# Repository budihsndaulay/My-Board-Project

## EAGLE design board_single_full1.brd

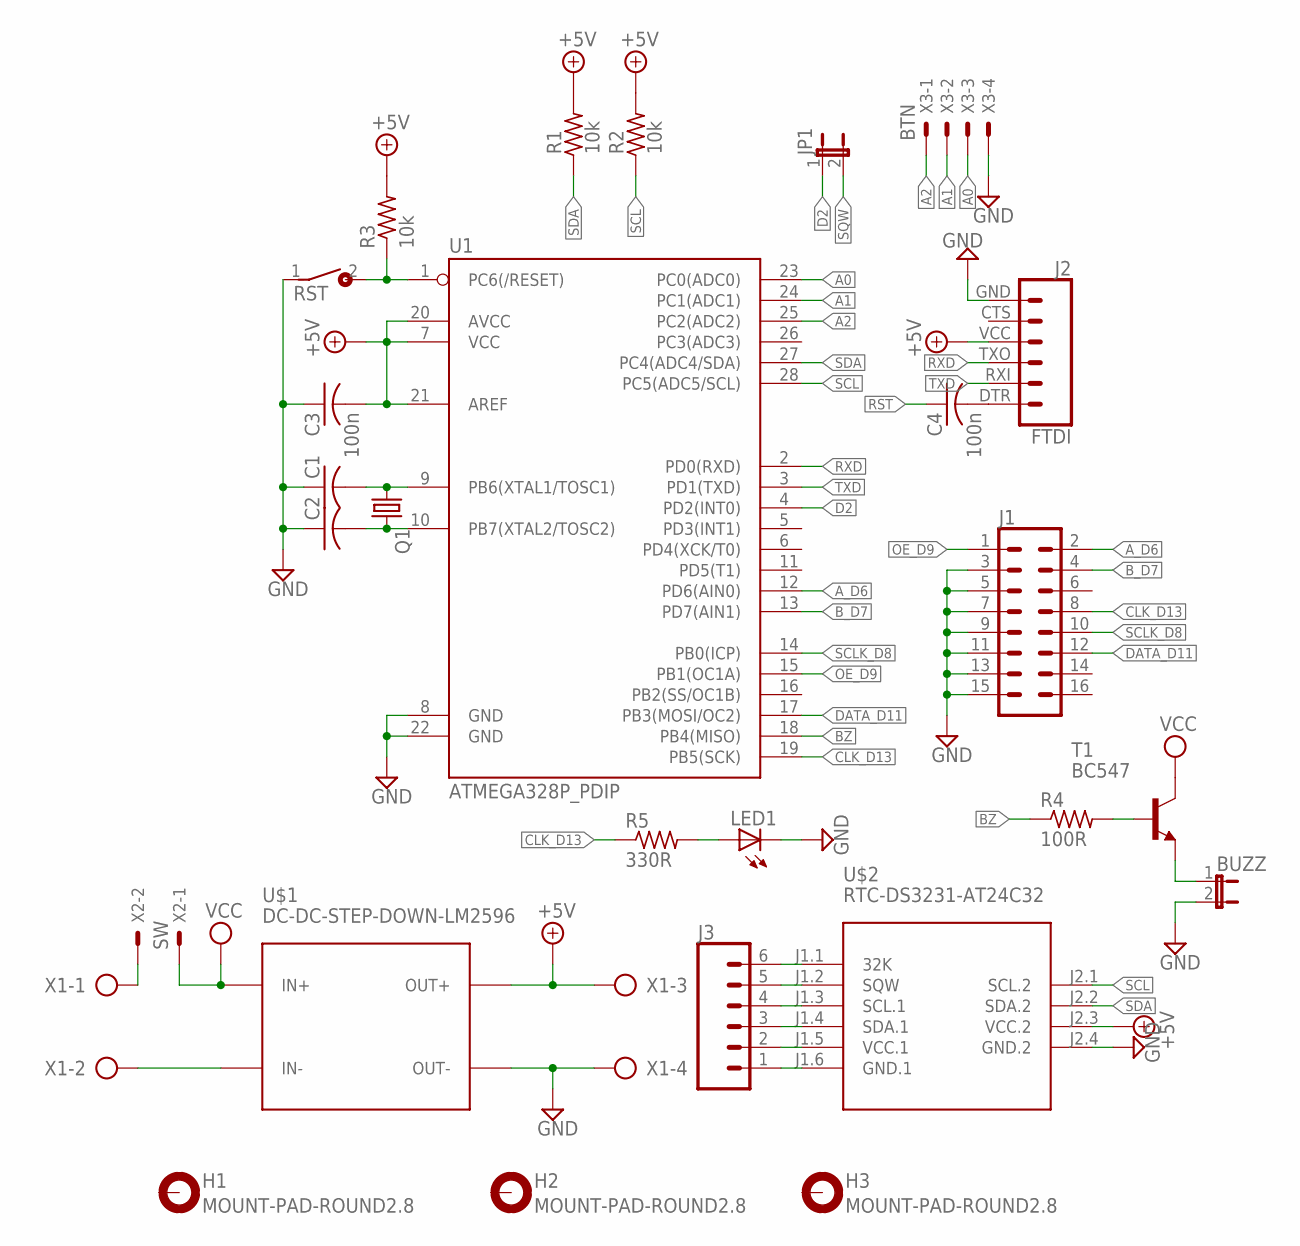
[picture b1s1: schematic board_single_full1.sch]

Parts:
BUZZ: JP1E; JP1
C1, C2: C-USC0603K; C0603K
C3, C4: 100n; C0603K
H1, H2, H3: MOUNT-PAD-ROUND2.8; 2,8-PAD
J1: CONN_08X2_SHROUD; 2X8-SHROUDED_LOCK
J2: FTDI; FTDI_BASIC
J3: CONN_06NO_SILK_FEMALE_PTH; 1X06_NO_SILK
JP1: JP1E; JP1
LED1: LED3MM
Q1: CRYSTALHC49U-V; HC49U-V
R1, R2: 10k; 0207/7
R3: 10k; R0603
R4: 100R; R0603
R5: 330R; R0603
RST: DS01E; DS-01
T1: BC547; TO92
U1: ATMEGA328P_PDIP; DIL28-3
U$1: DC-DC-STEP-DOWN-LM2596
U$2: RTC-DS3231-AT24C32
X1: AK500/4
X2: SW; JST-XH-02-PACKAGE-LONG-PAD
X3: BTN; JST-XH-04-PACKAGE-LONG-PAD

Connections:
+5V: C3.2, J2.VCC (4), R1.2, R2.2, R3.2, U1.7 (VCC), U1.20 (AVCC), U1.21 (AREF), U$1.OUT+, U$2.J2.3 (VCC.2), X1.3
A0: U1.23 (PC0(ADC0)), X3.3
A1: U1.24 (PC1(ADC1)), X3.2
A2: U1.25 (PC2(ADC2)), X3.1
A_D6: J1.2, U1.12 (PD6(AIN0))
BZ: R4.1, U1.18 (PB4(MISO))
B_D7: J1.4, U1.13 (PD7(AIN1))
CLK_D13: J1.8, R5.1, U1.19 (PB5(SCK))
D2: JP1.1, U1.4 (PD2(INT0))
DATA_D11: J1.12, U1.17 (PB3(MOSI/OC2))
GND: BUZZ.2, C1.1, C2.1, C3.1, J1.3, J1.5, J1.7, J1.9, J1.11, J1.13, J1.15, J2.GND (6), LED1.K (C), RST.1, U1.8 (GND), U1.22 (GND), U$1.OUT-, U$2.J2.4 (GND.2), X1.4, X3.4
unnamed: X1.1, X2.2
unnamed: U$1.IN-, X1.2
unnamed: BUZZ.1, T1.1 (E)
unnamed: C1.2, Q1.1, U1.9 (PB6(XTAL1/TOSC1))
unnamed: C2.2, Q1.2, U1.10 (PB7(XTAL2/TOSC2))
unnamed: C4.2, J2.DTR (1)
unnamed: J3.1, U$2.J1.6 (GND.1)
unnamed: J3.2, U$2.J1.5 (VCC.1)
unnamed: J3.3, U$2.J1.4 (SDA.1)
unnamed: J3.4, U$2.J1.3 (SCL.1)
unnamed: R4.2, T1.2 (B)
unnamed: J3.6, U$2.J1.1 (32K)
unnamed: LED1.A, R5.2
OE_D9: J1.1, U1.15 (PB1(OC1A))
RST: C4.1, R3.1, RST.2, U1.1 (PC6(/RESET))
RXD: J2.TXO (3), U1.2 (PD0(RXD))
SCL: R2.1, U1.28 (PC5(ADC5/SCL)), U$2.J2.1 (SCL.2)
SCLK_D8: J1.10, U1.14 (PB0(ICP))
SDA: R1.1, U1.27 (PC4(ADC4/SDA)), U$2.J2.2 (SDA.2)
SQW: J3.5, JP1.2, U$2.J1.2 (SQW)
TXD: J2.RXI (2), U1.3 (PD1(TXD))
VCC: T1.3 (C), U$1.IN+, X2.1

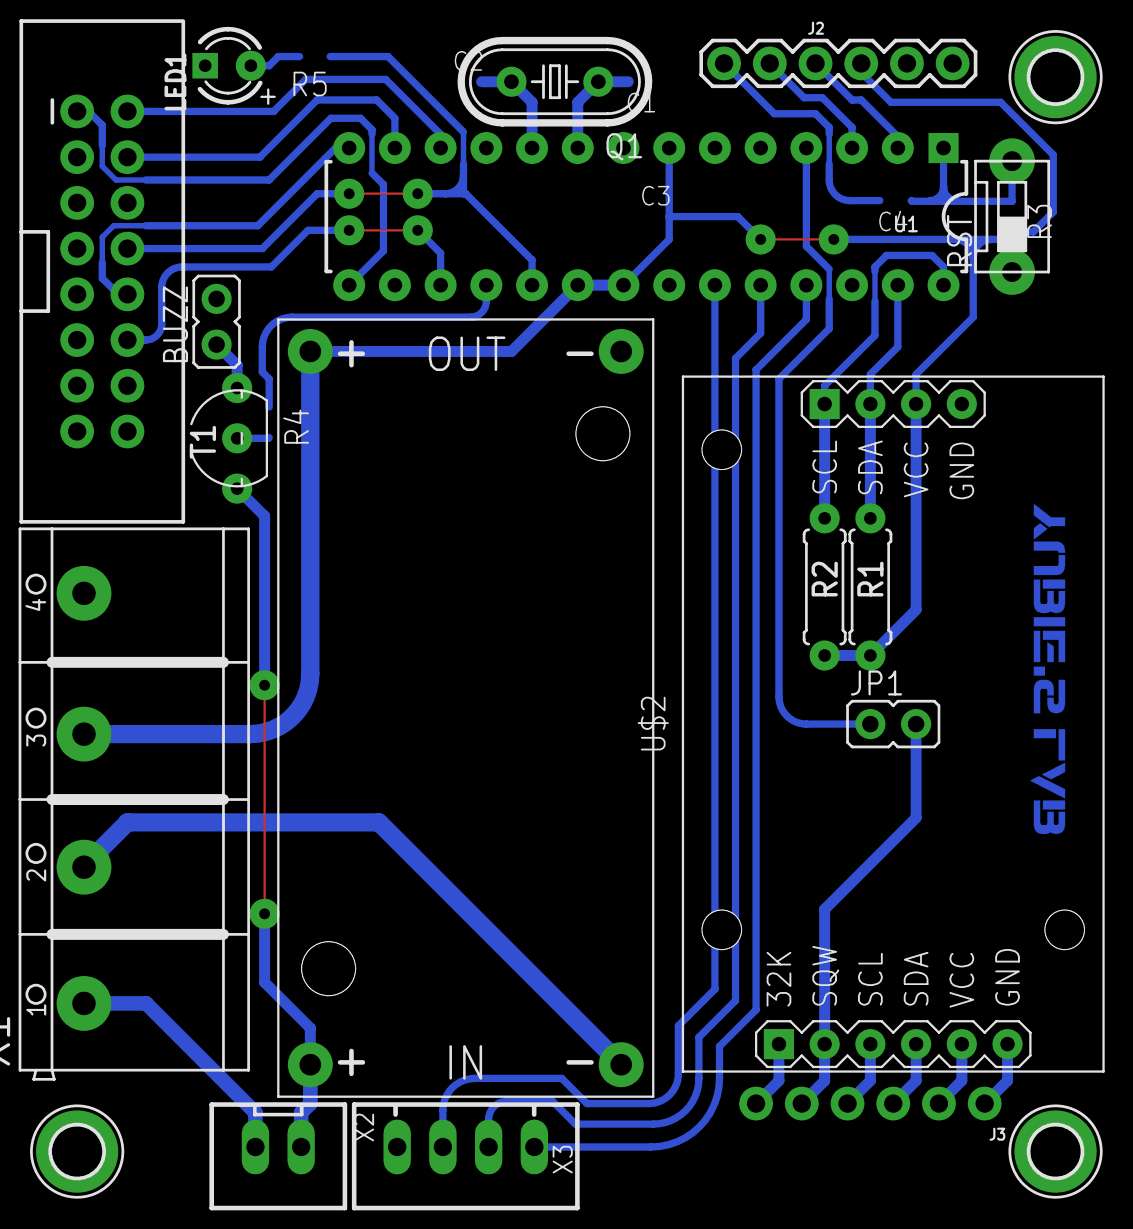
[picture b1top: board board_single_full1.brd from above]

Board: 2 copper layers, 27 parts (0 on the bottom side), 33 nets.

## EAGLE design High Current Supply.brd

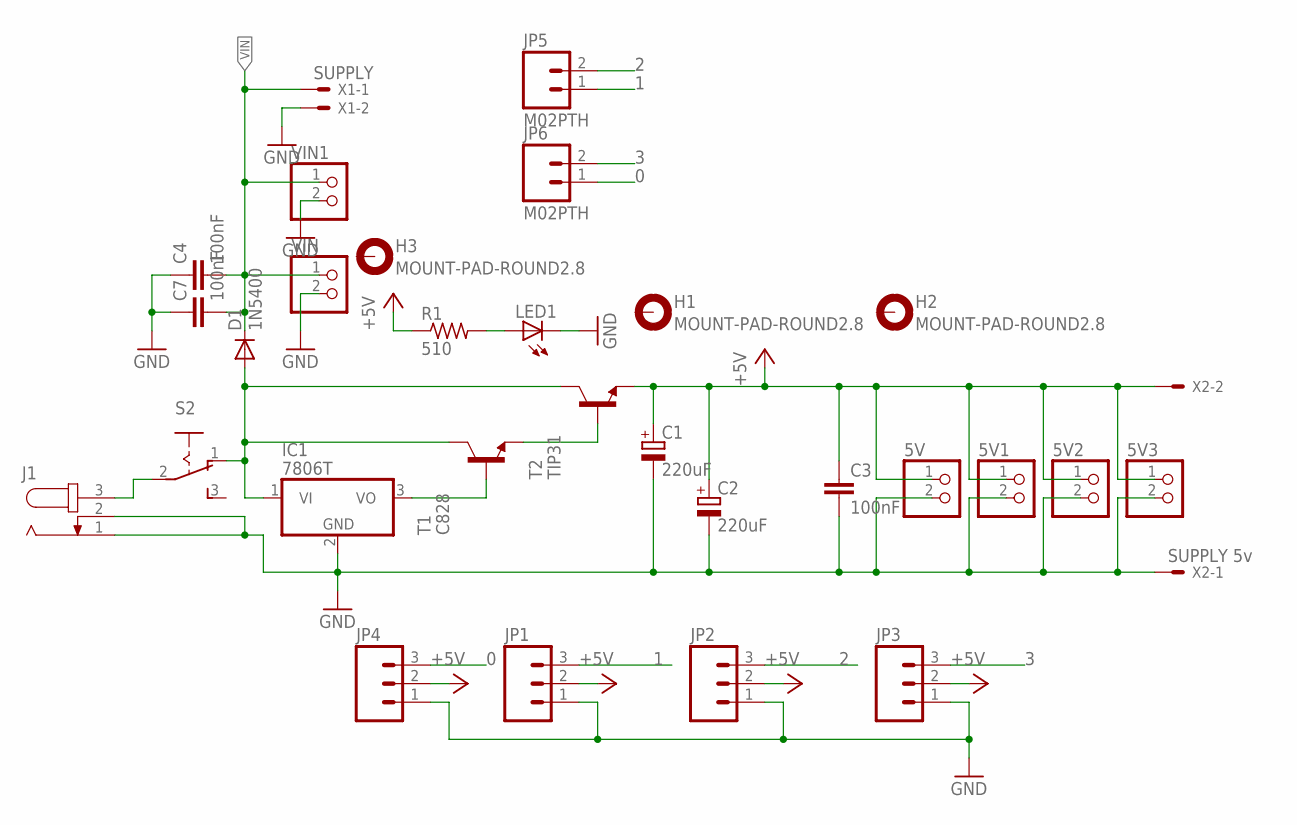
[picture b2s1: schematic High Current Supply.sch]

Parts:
5V, 5V1, 5V2, 5V3: PINHD-1X2; 1X02
C1, C2: 220uF; E2,5-7
C3, C4, C7: 100nF; C5B3
D1: 1N5400; DO201-15
H1, H2, H3: MOUNT-PAD-ROUND2.8; 2,8-PAD
IC1: 7806T; TO220H
J1: JACK-PLUG1; SPC4078
JP1, JP2, JP3, JP4: M03PTH; 1X03
JP5, JP6: M02PTH; 1X02
LED1: LED3MM
R1: 510; R0603
S2: 255SB
T1: C828; TO92-ECB
T2: TIP31; TO220
VIN, VIN1: PINHD-1X2; 1X02
X1: SUPPLY; JST-XH-02-PACKAGE-LONG-PAD
X2: SUPPLY 5v; JST-XH-02-PACKAGE-LONG-PAD

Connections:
0: JP4.3, JP6.1
1: JP1.3, JP5.1
2: JP2.3, JP5.2
3: JP3.3, JP6.2
+5V: 5V.1, 5V1.1, 5V2.1, 5V3.1, C1.+, C2.+, C3.1, JP1.2, JP2.2, JP3.2, JP4.2, R1.1, T2.3 (E), X2.2
GND: 5V.2, 5V1.2, 5V2.2, 5V3.2, C1.-, C2.-, C3.2, C4.1, C7.1, IC1.2 (GND), J1.1, J1.2, JP1.1, JP2.1, JP3.1, JP4.1, LED1.K (C), VIN.2, VIN1.2, X1.2, X2.1
unnamed: T1.E, T2.1 (B)
unnamed: J1.3, S2.2
unnamed: IC1.3 (VO), T1.B
unnamed: D1.A, IC1.1 (VI), S2.1 (O), T1.C, T2.2 (C)
unnamed: LED1.A, R1.2
VIN: C4.2, C7.2, D1.C, VIN.1, VIN1.1, X1.1

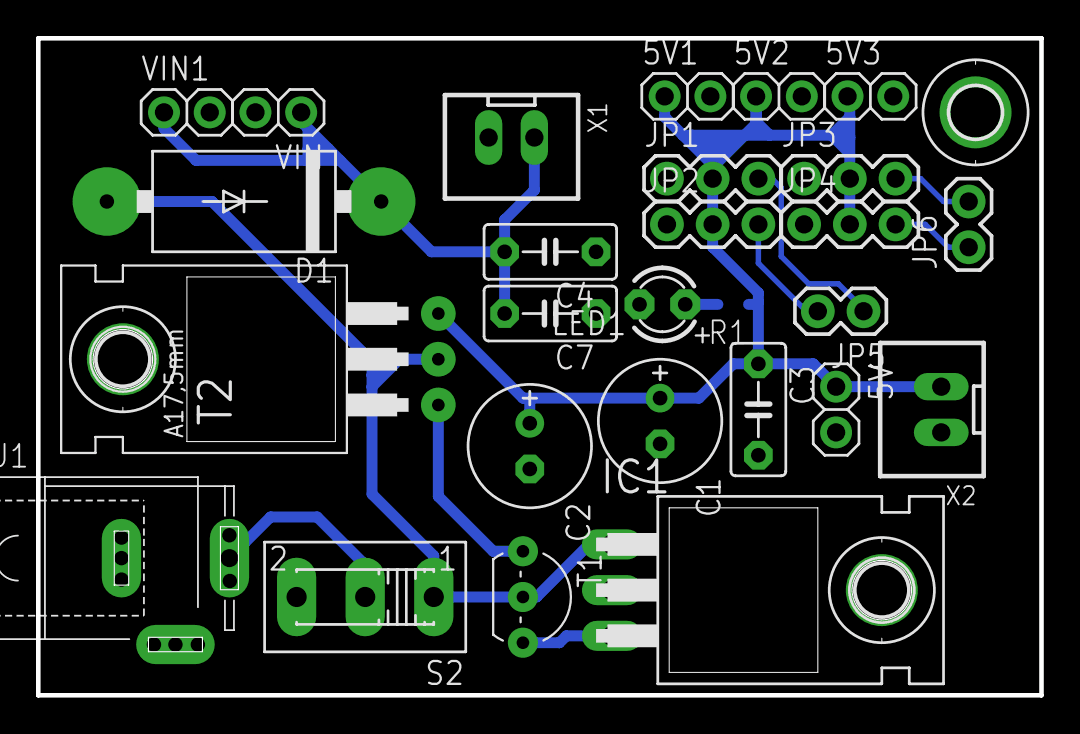
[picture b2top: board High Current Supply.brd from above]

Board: 2 copper layers, 55.7 x 36.5 mm, 30 parts (0 on the bottom side), 12 nets.

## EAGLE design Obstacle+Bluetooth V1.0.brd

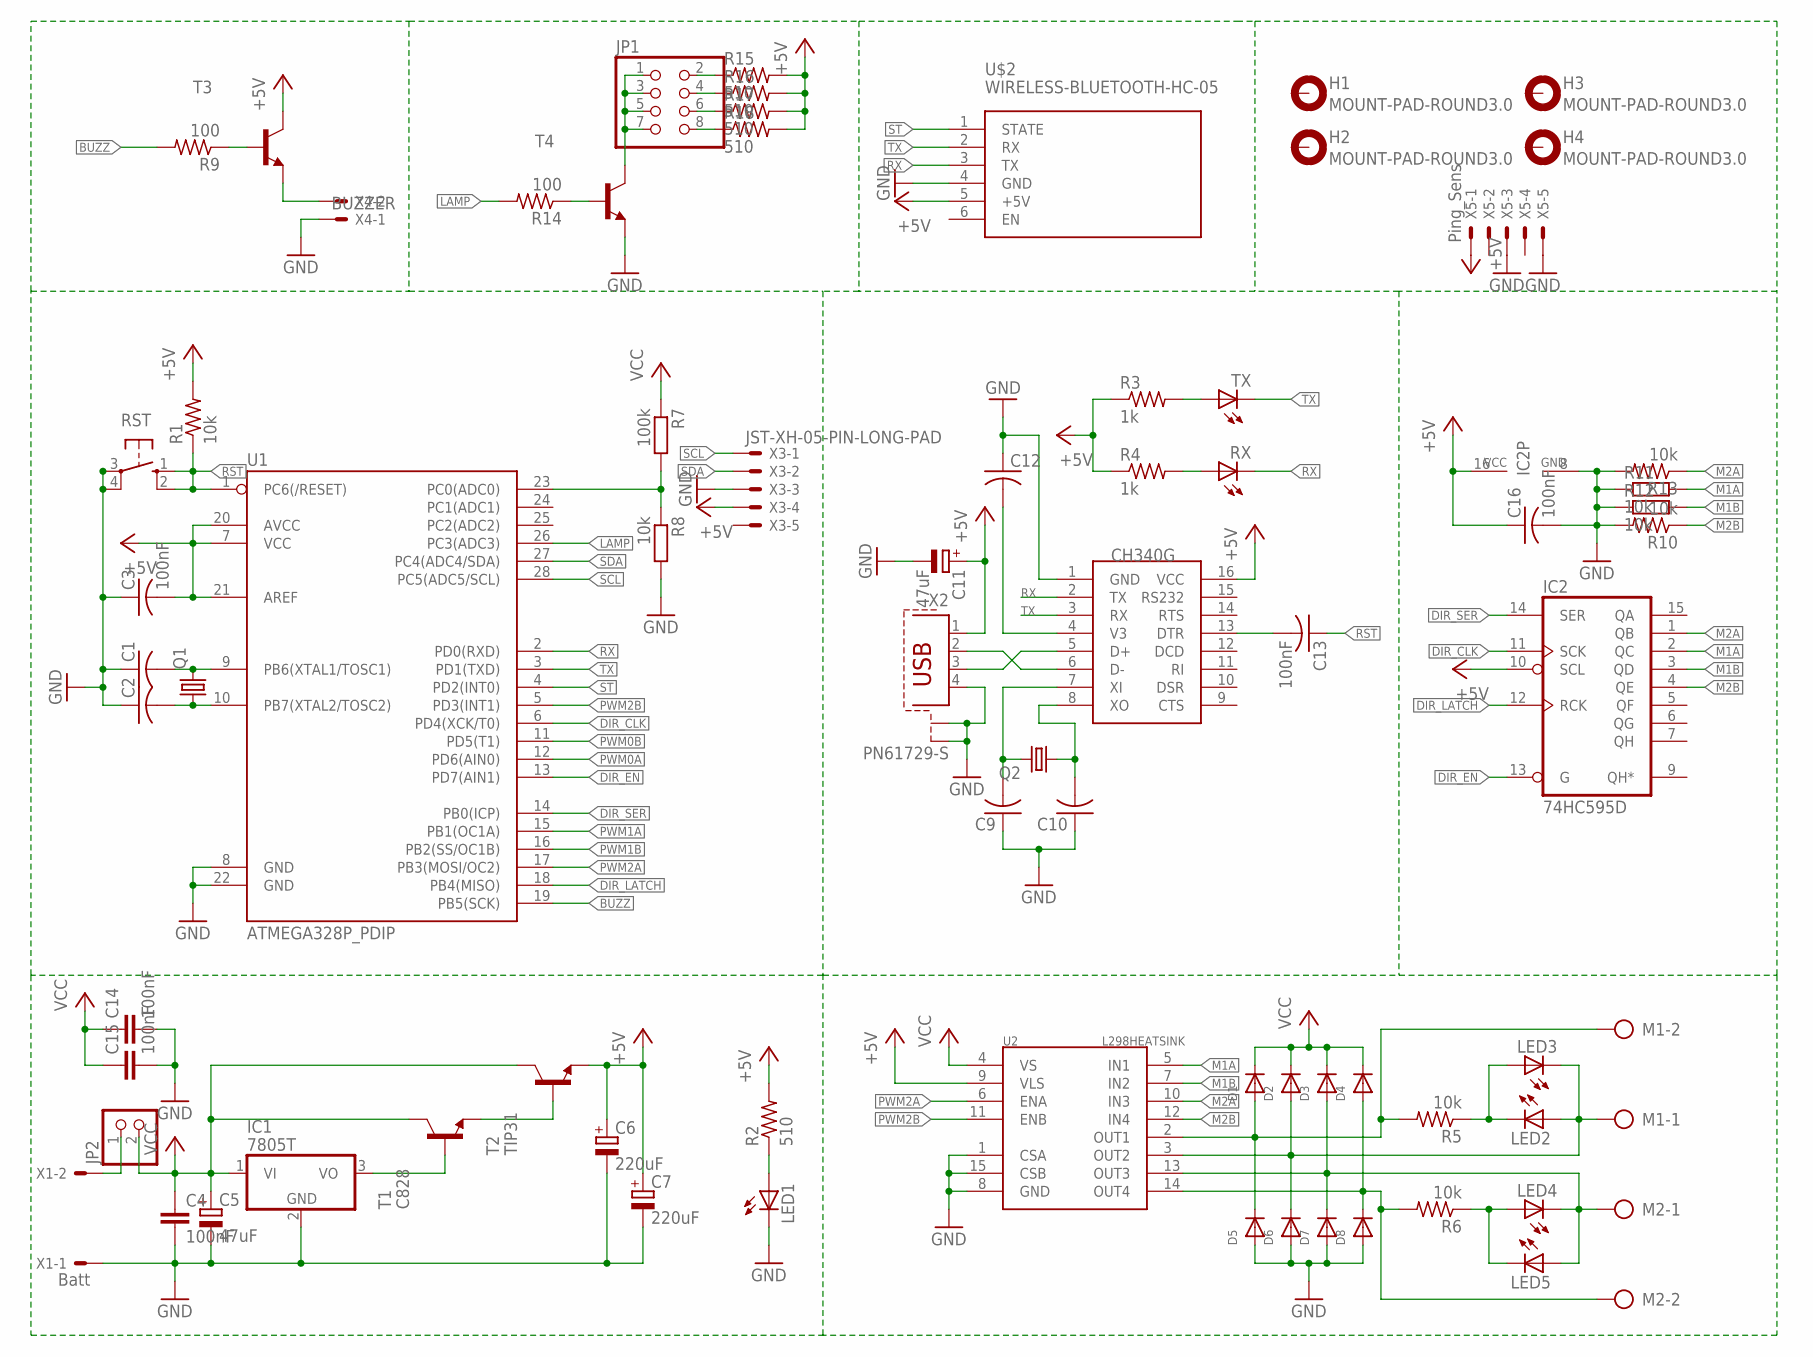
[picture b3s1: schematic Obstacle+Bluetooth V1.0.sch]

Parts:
C1, C2, C9, C10, C12: C-USC0603K; C0603K
C3, C13, C16: 100nF; C0603K
C4, C14, C15: 100nF; C5B2.5
C5, C11: 47uF; E2,5-7
C6, C7: 220uF; E2,5-5
D1, D2, D3, D4, D5, D6, D7, D8: DIODESMA; SMADIODE
H1, H2, H3, H4: MOUNT-PAD-ROUND3.0; 3,0-PAD
IC1: 7805T; TO220H
IC2: 74HC595D; SO16
JP1: PINHD-2X4; 2X04
JP2: PINHD-1X2; 1X02
LED1, LED2, LED3, LED4, LED5: LED3MM
M1, M2: AK500/2
Q1, Q2: CRYSTALHC49U-V; HC49U-V
R1, R5, R6, R10, R13: 10k; R0603
R2, R15, R16, R17, R18: 510; R0603
R3, R4: 1k; R0603
R7: 100k; 0207/7
R8, R11, R12: 10k; 0207/7
R9, R14: 100; R0603
RST: 10-XX; B3F-10XX
RX: LED3MM
T1: C828; TO92-ECB
T2: TIP31; TO220
T3, T4: -NPN-TO92L; TO92L
TX: LED3MM
U1: ATMEGA328P_PDIP; DIL28-3
U2: L298HEATSINK; MULTIWATT15_6400BGHEATSINK
U$1: CH340G; SOIC16
U$2: WIRELESS-BLUETOOTH-HC-05
X1: Batt; JST-XH-02-PACKAGE-LONG-PAD
X2: PN61729-S
X3: JST-XH-05-PIN-LONG-PAD; JST-XH-05-PACKAGE-LONG-PAD
X4: BUZZER; JST-XH-02-PACKAGE-LONG-PAD
X5: Ping_Sens; JST-XH-05-PACKAGE-LONG-PAD

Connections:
+5V: C3.2, C6.+, C7.+, C11.+, C16.1, IC2.10 (SCL), IC2.16 (VCC), R1.2, R2.2, R3.1, R4.1, R15.2, R16.2, R17.2, R18.2, T2.3 (E), T3.3 (C), U1.7 (VCC), U1.20 (AVCC), U1.21 (AREF), U2.9 (VLS), U$1.16 (VCC), U$2.5 (+5V), X2.1, X3.4, X5.1
BUZZ: R9.2, U1.19 (PB5(SCK))
DIR_CLK: IC2.11 (SCK), U1.6 (PD4(XCK/T0))
DIR_EN: IC2.13 (G), U1.13 (PD7(AIN1))
DIR_LATCH: IC2.12 (RCK), U1.18 (PB4(MISO))
DIR_SER: IC2.14 (SER), U1.14 (PB0(ICP))
GND: C1.1, C2.1, C3.1, C4.2, C5.-, C6.-, C7.-, C9.1, C10.1, C11.-, C12.1, C14.2, C15.2, C16.2, D5.A, D6.A, D7.A, D8.A, IC1.2 (GND), IC2.8 (GND), LED1.K (C), R8.2, R10.2, R11.1, R12.1, R13.2, RST.3, RST.4 (P1), T4.1 (E), U1.8 (GND), U1.22 (GND), U2.1 (CSA), U2.8 (GND), U2.15 (CSB), U$1.1 (GND), U$2.4 (GND), X1.1, X2.4, X2.S1, X2.S2, X3.3, X4.1, X5.3, X5.5
LAMP: R14.2, U1.26 (PC3(ADC3))
M1A: IC2.2 (QC), R11.2, U2.5 (IN1)
M1B: IC2.3 (QD), R12.2, U2.7 (IN2)
M2A: IC2.1 (QB), R13.1, U2.10 (IN3)
M2B: IC2.4 (QE), R10.1, U2.12 (IN4)
unnamed: C1.2, Q1.2, U1.9 (PB6(XTAL1/TOSC1))
unnamed: C2.2, Q1.1, U1.10 (PB7(XTAL2/TOSC2))
unnamed: C13.2, U$1.13 (DTR)
unnamed: R4.2, RX.A
unnamed: IC1.3 (VO), T1.B
unnamed: T1.E, T2.1 (B)
unnamed: R3.2, TX.A
unnamed: LED1.A, R2.1
unnamed: U$1.6 (D-), X2.2
unnamed: U$1.5 (D+), X2.3
unnamed: C9.2, Q2.2, U$1.7 (XI)
unnamed: C10.2, Q2.1, U$1.8 (XO)
unnamed: D2.A, D6.C, LED2.A, LED3.K (C), M1.1, U2.3 (OUT2)
unnamed: D3.A, D7.C, LED4.K (C), LED5.A, M2.1, U2.13 (OUT3)
unnamed: C12.2, U$1.4 (V3)
unnamed: D4.A, D8.C, M2.2, R6.2, U2.14 (OUT4)
unnamed: LED2.K (C), LED3.A, R5.1
unnamed: LED4.A, LED5.K (C), R6.1
unnamed: R7.2, R8.1, U1.23 (PC0(ADC0))
unnamed: T3.1 (E), X4.2
unnamed: R9.1, T3.2 (B)
unnamed: R14.1, T4.2 (B)
unnamed: JP2.1, X1.2
unnamed: JP1.1, JP1.3, JP1.5, JP1.7, T4.3 (C)
unnamed: JP1.2, R15.1
unnamed: JP1.4, R16.1
unnamed: JP1.6, R17.1
unnamed: JP1.8, R18.1
unnamed: D1.A, D5.C, M1.2, R5.2, U2.2 (OUT1)
PWM0A: U1.12 (PD6(AIN0))
PWM0B: U1.11 (PD5(T1))
PWM1A: U1.15 (PB1(OC1A))
PWM1B: U1.16 (PB2(SS/OC1B))
PWM2A: U1.17 (PB3(MOSI/OC2)), U2.6 (ENA)
PWM2B: U1.5 (PD3(INT1)), U2.11 (ENB)
RST: C13.1, R1.1, RST.1 (S), RST.2 (S1), U1.1 (PC6(/RESET))
RX: RX.K (C), U1.2 (PD0(RXD)), U$1.2 (TX), U$2.3 (TX)
SCL: U1.28 (PC5(ADC5/SCL)), X3.1
SDA: U1.27 (PC4(ADC4/SDA)), X3.2
ST: U1.4 (PD2(INT0)), U$2.1 (STATE)
TX: TX.K (C), U1.3 (PD1(TXD)), U$1.3 (RX), U$2.2 (RX)
VCC: C4.1, C5.+, C14.1, C15.1, D1.C, D2.C, D3.C, D4.C, IC1.1 (VI), JP2.2, R7.1, T1.C, T2.2 (C), U2.4 (VS)

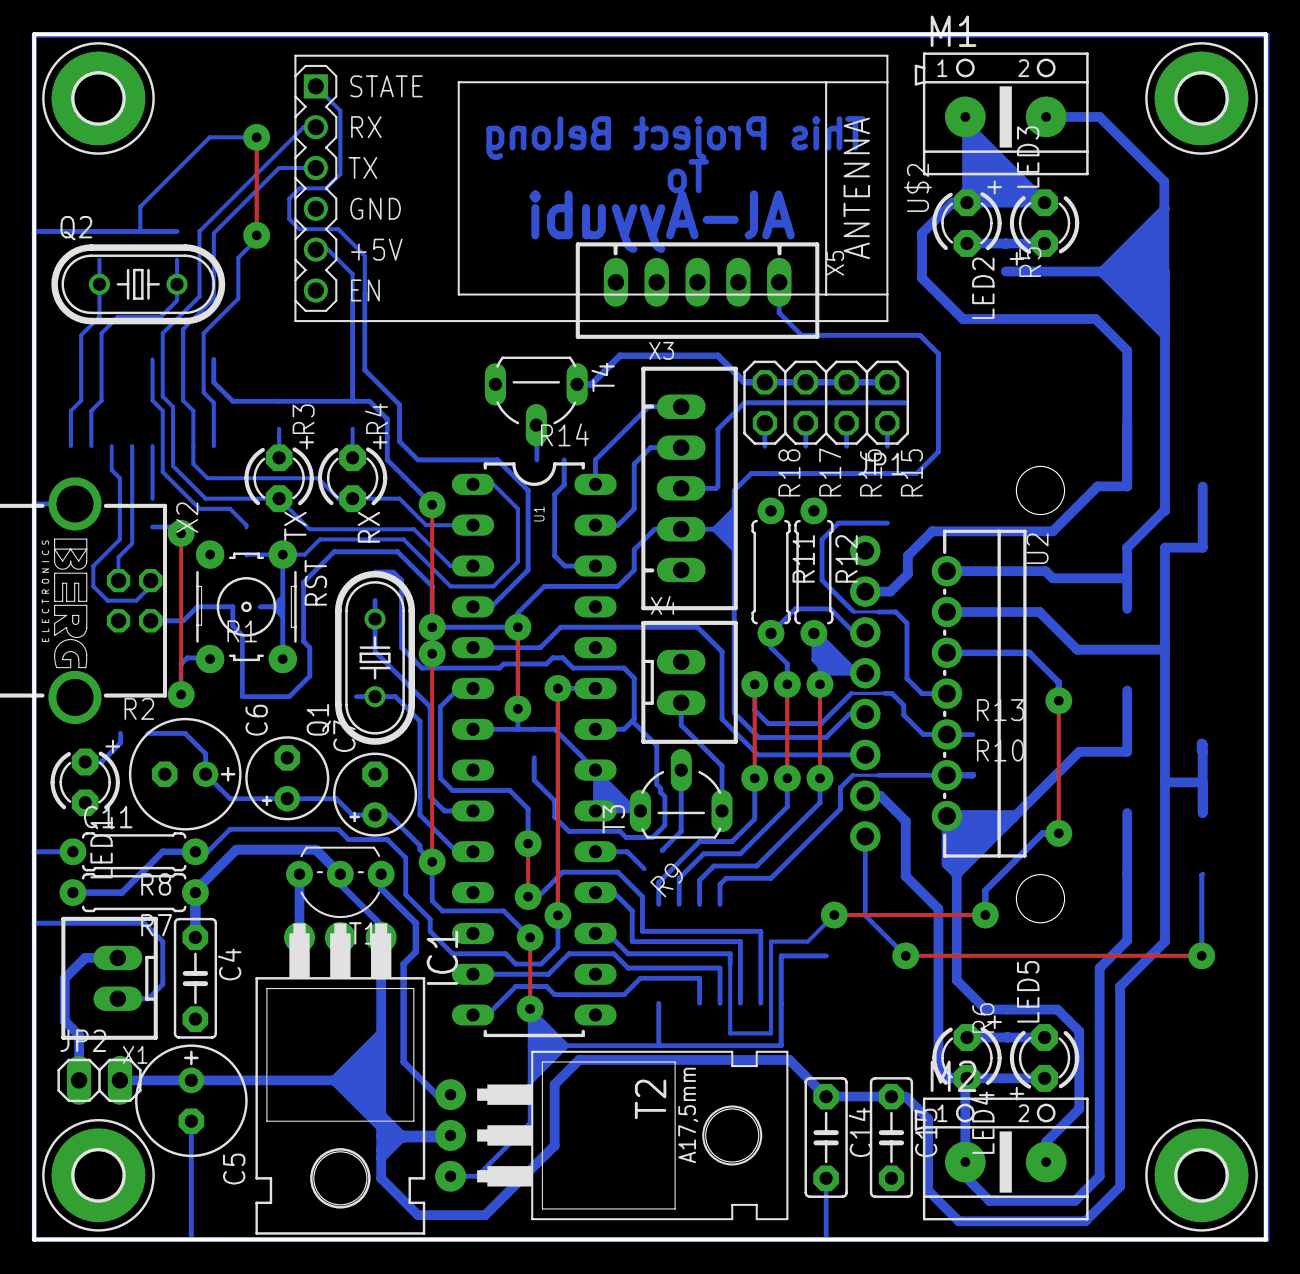
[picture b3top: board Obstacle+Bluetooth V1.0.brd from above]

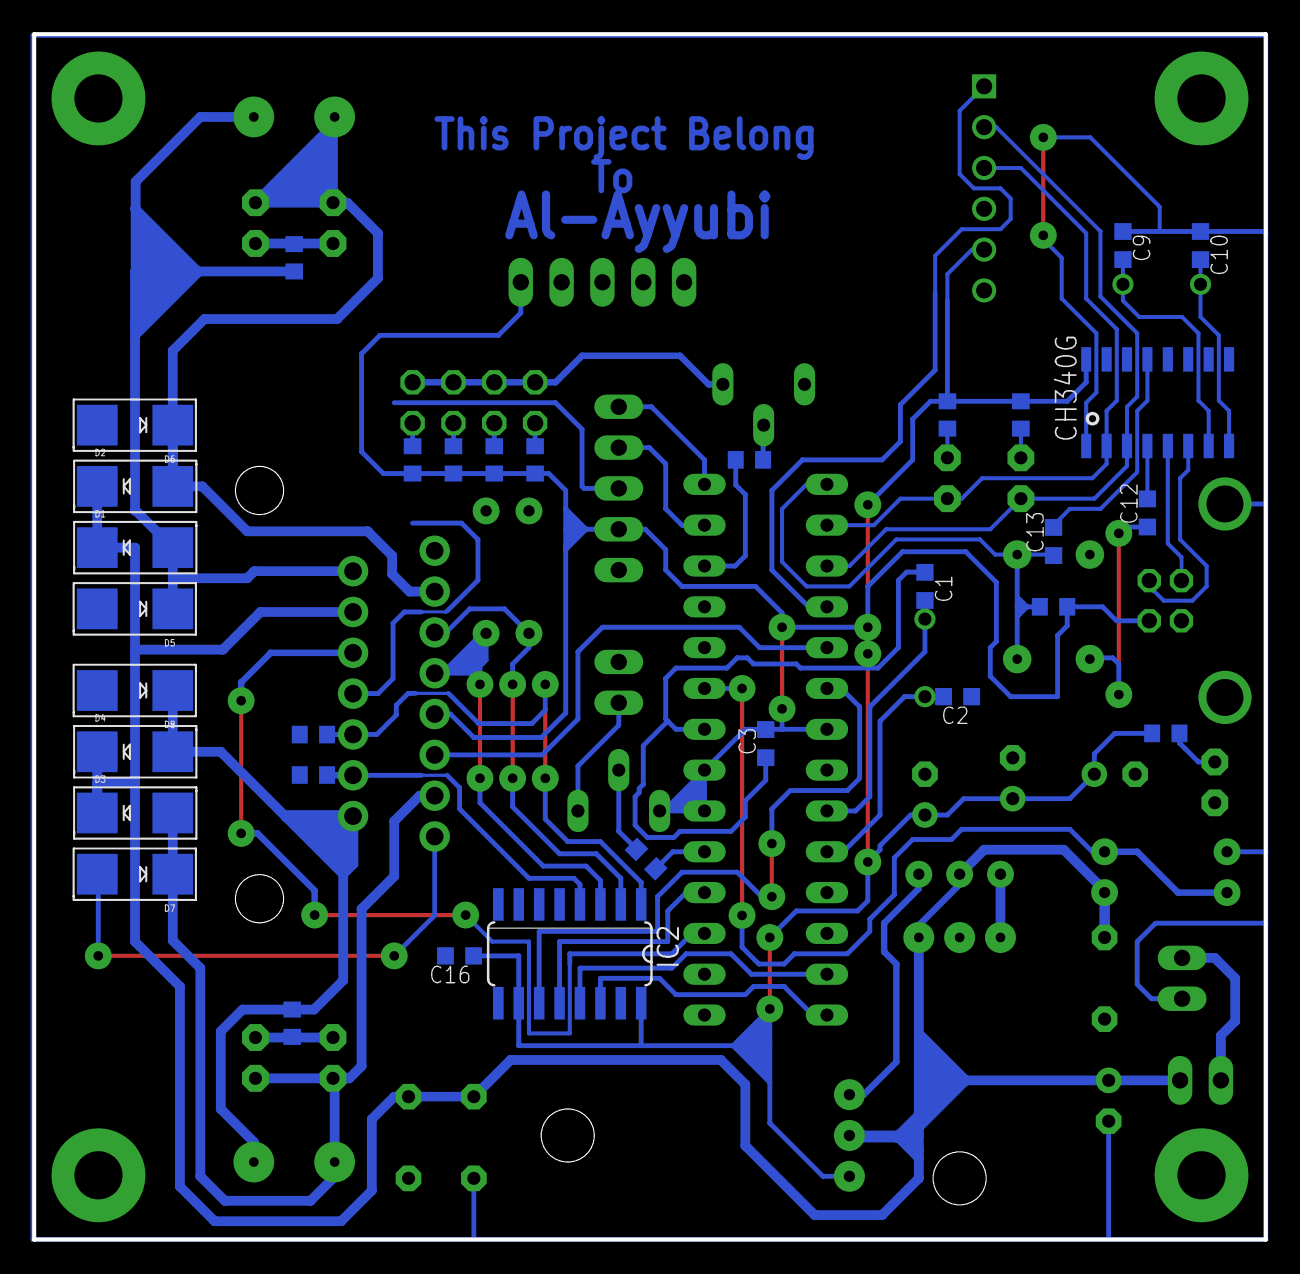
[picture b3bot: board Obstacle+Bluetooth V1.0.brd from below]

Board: 2 copper layers, 76.6 x 75.0 mm, 74 parts (18 on the bottom side), 50 nets.

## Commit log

2019-09-04 Add files via upload
    My obstacle robot project
2020-04-05 Create Power Supply
2025-08-05 PCB panel P10 controller
    Panel P10 Controller With ATMega328P DIP IC

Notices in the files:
parts and their libraries:
SparkFun-Connectors: Licensing: Creative Commons ShareAlike 4.0 International - https://creativecommons.org/licenses/by-sa/4.0
diy-modules: Released under the Creative Commons Attribution 4.0 International License: http://creativecommons.org/licenses/by/4.0
